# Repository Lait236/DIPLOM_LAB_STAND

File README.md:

В DIPLOM_LAB_STAND_SCHEMES находятся принципиальные схемы стенда и разводки плат в вариантах с модулями (с использованием заливки земли полигоном ..._gnd или без заливки) и без них (тоже с заливкой полигоном и без неё).

DIPLOM.kicad_sch - Принципиальная схема управляющей платы.

пс_плата_2.kicad_sch - Принципиальная платы расширенной периферии.

DIPLOM.kicad_pcb - Разводка управляющей платы.

DIPLOM_BOARD2.kicad_pcb - Разводка платы расширенной периферии.

В DIPLOM_LAB_STAND находятся файлы проекта для Microchip Studio. 

В DEBUG находится .hex файл для прошивки микроконтроллера. 

DIPLOM_LAB_STAND.atsln - сам проект.

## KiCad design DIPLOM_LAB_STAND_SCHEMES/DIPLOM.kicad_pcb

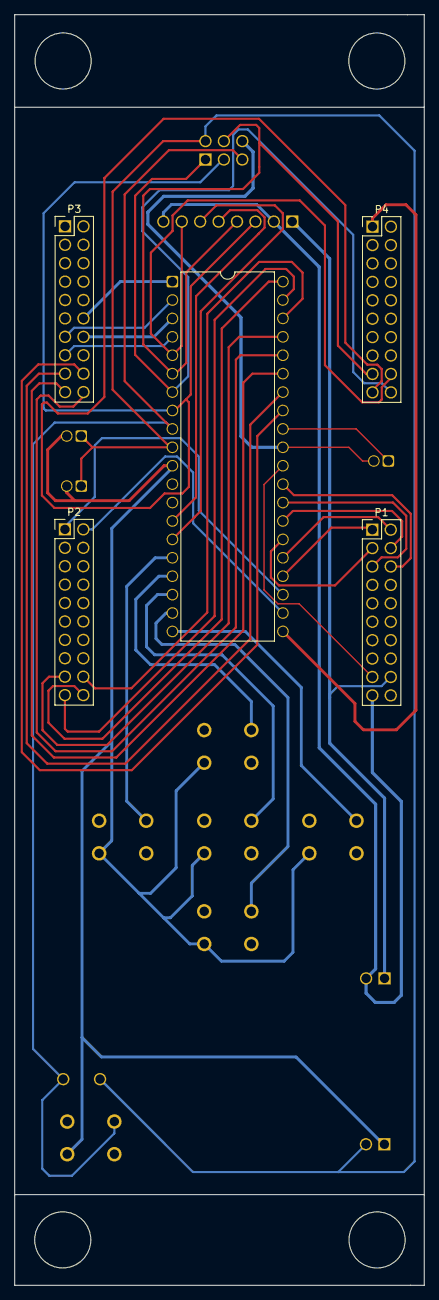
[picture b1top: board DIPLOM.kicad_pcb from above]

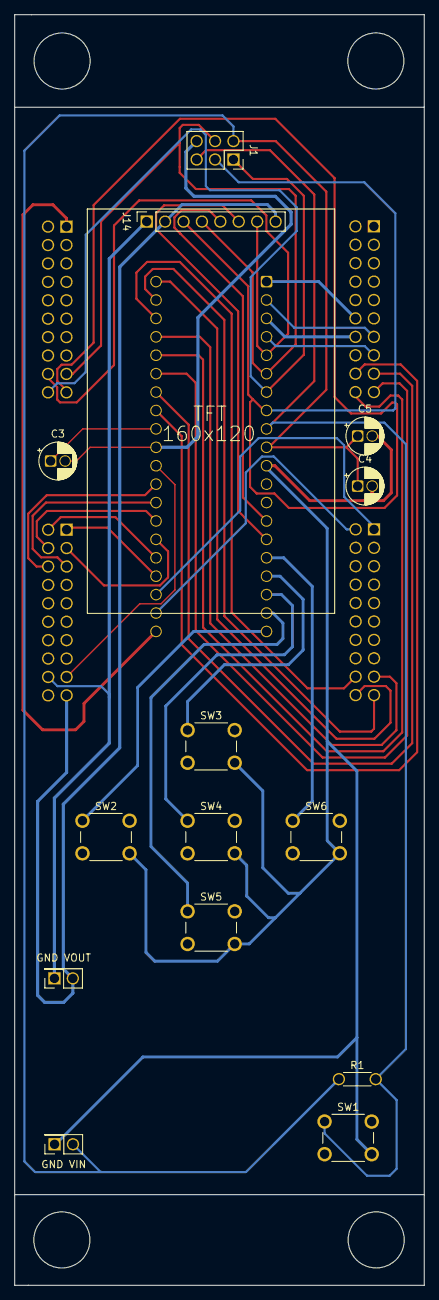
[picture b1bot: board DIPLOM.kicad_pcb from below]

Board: 2 copper layers, 56.5 x 150.0 mm, 19 parts (14 on the bottom side), 37 nets.

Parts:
C3, C5: 0.1uF; CP_Radial_D5.0mm_P2.00mm
C4: 10uF; CP_Radial_D5.0mm_P2.00mm
GND VIN: PinSocket_2x01_P2.54mm_Vertical
GND VOUT: PinSocket_2x01_P2.54mm_Vertical
J1: USBASP_PINS; PinSocket_2x03_P2.54mm_Vertical
J14: display_out; PinSocket_1x08_P2.54mm_Vertical
P1, P2, P3, P4: PinHeader_2x10_P2.54mm_Vertical
R1: 10k; R_Axial_DIN0204_L3.6mm_D1.6mm_P5.08mm_Horizontal
SW1: BTN_RST; SW_PUSH_6mm
SW2: BTN_L; SW_PUSH_6mm
SW3: BTN_UP; SW_PUSH_6mm
SW4: BTN_CENTER; SW_PUSH_6mm
SW5: BTN_DOWN; SW_PUSH_6mm
SW6: BTN_R; SW_PUSH_6mm
U5: ATmega1284P-P; DIP-40_W15.24mm

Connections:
+3.3v: GND VOUT.2, J14.2, J14.8, P1.19
+5.0v: C4.1, C5.1, GND VIN.2, J1.2 (VCC), P1.17, R1.1, U5.10 (VCC), U5.30 (AVCC)
GND: C3.2, C4.2, C5.2, GND VIN.1, GND VOUT.1, J1.6 (GND), J14.1, P1.18, SW1.1 (A), SW1.2 (A), SW2.2 (A), SW3.2 (A), SW4.2 (A), SW5.2 (A), SW6.2 (A), U5.11 (GND), U5.31 (GND)
unnamed: J1.1 (MISO), P4.20, U5.7 (PB6)
unnamed: J1.4 (MOSI), J14.4, P4.17, U5.6 (PB5)
unnamed: J1.3 (SCK), J14.3, P4.19, U5.8 (PB7)
unnamed: J1.5 (~RST), R1.2, SW1.1 (A), U5.9 (~RESET)
unnamed: P2.20, U5.40 (PA0)
unnamed: P2.19, U5.39 (PA1)
unnamed: P2.18, U5.38 (PA2)
unnamed: P2.17, U5.37 (PA3)
unnamed: P3.20, U5.36 (PA4)
unnamed: P3.19, U5.35 (PA5)
unnamed: P3.17, U5.34 (PA6)
unnamed: P3.18, U5.33 (PA7)
unnamed: P3.12, U5.1 (PB0)
unnamed: P3.13, U5.2 (PB1)
unnamed: P3.14, U5.3 (PB2)
unnamed: P3.15, U5.4 (PB3)
unnamed: P2.2, U5.22 (PC0)
unnamed: P2.1, U5.23 (PC1)
unnamed: P1.1, U5.24 (PC2)
unnamed: P1.2, U5.25 (PC3)
unnamed: P1.3, U5.26 (PC4)
unnamed: P1.4, U5.27 (PC5)
unnamed: P1.5, U5.28 (PC6)
unnamed: P1.6, U5.29 (PC7)
unnamed: P4.1, U5.21 (PD7)
unnamed: J14.7, P4.18, U5.5 (PB4)
unnamed: J14.5, U5.14 (PD0)
unnamed: J14.6, U5.15 (PD1)
unnamed: C3.1, U5.32 (AREF)
unnamed: SW6.1 (A), SW6.2 (A), U5.16 (PD2)
unnamed: SW3.1 (A), SW3.2 (A), U5.17 (PD3)
unnamed: SW4.1 (A), SW4.2 (A), U5.18 (PD4)
unnamed: SW5.1 (A), SW5.2 (A), U5.19 (PD5)
unnamed: SW2.1 (A), SW2.2 (A), U5.20 (PD6)

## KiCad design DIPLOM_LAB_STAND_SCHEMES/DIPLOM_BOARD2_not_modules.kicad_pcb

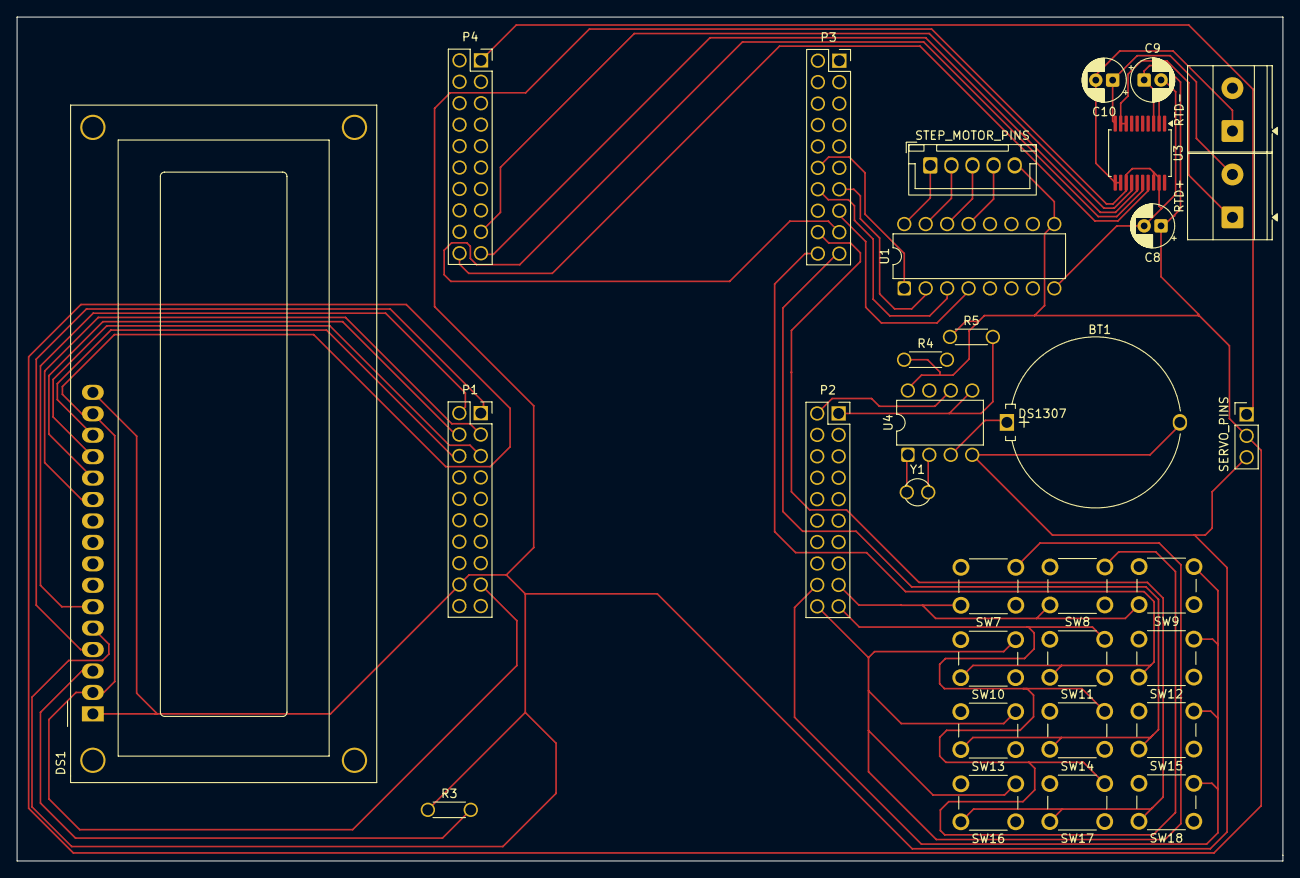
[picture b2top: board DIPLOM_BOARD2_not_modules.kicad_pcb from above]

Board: 2 copper layers, 150.0 x 100.0 mm, 32 parts (0 on the bottom side), 33 nets.

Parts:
BT1: Battery 3V; Battery_Panasonic_CR2032-HFN_Horizontal_CircularHoles
C8, C9: 0.1uF; CP_Radial_D5.0mm_P2.00mm
C10: 100nF; CP_Radial_D5.0mm_P2.00mm
DS1: WC1602A
P1, P2, P3, P4: PinSocket_2x10_P2.54mm_Vertical
R3: 2k; R_Axial_DIN0204_L3.6mm_D1.6mm_P5.08mm_Horizontal
R4, R5: 4.7k; R_Axial_DIN0204_L3.6mm_D1.6mm_P5.08mm_Horizontal
RTD+: TerminalBlock_Phoenix_MKDS-1,5-2-5.08_1x02_P5.08m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; TerminalBlock_Phoenix_MKDS-1,5-2-5.08_1x02_P5.08mm_Horizont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
RTD-: TerminalBlock_Phoenix_MKDS-1,5-2-5.08_1x02_P5.08m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; TerminalBlock_Phoenix_MKDS-1,5-2-5.08_1x02_P5.08mm_Horizont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
SERVO_PINS: PinHeader_1x03_P2.54mm_Vertical
STEP_MOTOR_PINS: JST_XH_B5B-XH-A_1x05_P2.50mm_Vertical
SW7: 1; SW_PUSH_6mm
SW8: 2; SW_PUSH_6mm
SW9: 3; SW_PUSH_6mm
SW10: 4; SW_PUSH_6mm
SW11: 5; SW_PUSH_6mm
SW12: 6; SW_PUSH_6mm
SW13: 7; SW_PUSH_6mm
SW14: 8; SW_PUSH_6mm
SW15: 9; SW_PUSH_6mm
SW16: *; SW_PUSH_6mm
SW17: 0; SW_PUSH_6mm
SW18: #; SW_PUSH_6mm
U1: ULN2003; DIP-16_W7.62mm
U3: MAX31865xAP; SSOP-20_5.3x7.2mm_P0.65mm
U4: DS1307; DIP-8_W7.62mm
Y1: 32.768kHz; Crystal_AT310_D3.0mm_L10.0mm_Vertical

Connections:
+5.0v: C8.1, C9.1, DS1.2 (VDD), DS1.15 (LED(+)), P1.17, R4.1, R5.1, SERVO_PINS.2, STEP_MOTOR_PINS.5, U1.9 (COM), U3.2 (DVDD), U3.3 (VDD), U4.8 (VCC)
GND: BT1.2 (-), C8.2, C9.2, DS1.1 (VSS), DS1.5 (R/W), DS1.16 (LED(-)), P1.18, R3.1, SERVO_PINS.3, U1.8 (GND), U3.13 (GND), U3.18 (DGND), U3.19 (GND), U4.4 (GND)
unnamed: BT1.1 (+), U4.3 (VBAT)
unnamed: DS1.3 (VO), R3.2
unnamed: P4.20, U3.17 (SDO)
unnamed: P4.17, U3.14 (SDI)
unnamed: P4.19, U3.15 (SCLK)
unnamed: P2.20, SW7.2 (A), SW10.2 (A), SW13.2 (A), SW16.2 (A)
unnamed: P2.19, SW8.2, SW11.2, SW14.2, SW17.2
unnamed: P2.18, SW9.2, SW12.2, SW15.2, SW18.2
unnamed: P2.17, SW7.1 (A), SW8.1, SW9.1
unnamed: P3.20, SW10.1 (A), SW11.1, SW12.1
unnamed: P3.19, SW13.1 (A), SW14.1, SW15.1
unnamed: P3.18, SW16.1 (A), SW17.1, SW18.1
unnamed: P3.17, U3.16 (~CS)
unnamed: P3.12, U1.1 (I1)
unnamed: P3.13, U1.2 (I2)
unnamed: P3.14, U1.3 (I3)
unnamed: P3.15, U1.4 (I4)
unnamed: P2.2, R4.2, U4.6 (SCL)
unnamed: P2.1, R5.2, U4.5 (SDA)
unnamed: DS1.4 (RS), P1.1
unnamed: DS1.6 (E), P1.2
unnamed: DS1.11 (D4), P1.3
unnamed: DS1.12 (D5), P1.4
unnamed: DS1.13 (D6), P1.5
unnamed: DS1.14 (D7), P1.6
unnamed: P4.1, SERVO_PINS.1
unnamed: U3.4 (BIAS), U3.5 (REFIN+), U3.6 (REFIN-), U3.7 (ISENSOR)
unnamed: C10.1, RTD+.1, RTD+.2, U3.8 (FORCE+), U3.9 (FORCE2), U3.10 (RTDIN+)
unnamed: C10.2, RTD-.1, U3.11 (RTDIN-), U3.12 (FORCE-)
unnamed: U4.1 (X1), Y1.1
unnamed: U4.2 (X2), Y1.2

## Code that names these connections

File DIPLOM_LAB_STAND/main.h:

	/*
 * main.h
 *
 * Created: 02.04.2026 22:29:26
 *  Author: Владислав
 */ 


#ifndef MAIN_H_
#define MAIN_H_

// установка частоты

#define F_CPU 8000000UL

// подключение системных файлов библиотек

#include <avr/io.h> // стандартная библиотека инициализации AVR
#include <util/delay.h> // задержки
#include <stdint.h> // фиксированные целочисленные типы
#include <avr/pgmspace.h> // работа с памятью программ Flash || PROGMEM хранит большие таблицы не в SRAM, а во Flash, так как SRAM мало || обращение к Flash памяти идет через оператор &
#include <avr/interrupt.h> // работа с прерываниями

// замена имен лапок на макроподстановки для удобной инициализации spi для дисплея

#define LCD_SCK  PB7 // пин тактового сигнала SPI
#define LCD_MOSI PB5 // пин MOSI SPI
#define LCD_CS   PB4 // пин Chip Select дисплея подключён к PB2 || 0 — дисплей выбран и слушает SPI || 1 — дисплей игнорирует SPI
#define LCD_DC   PD1 // пин DC дисплея подключён к PD1 || DC = Data / Command || 0 — отправляем команду || 1 — отправляем данные
#define LCD_RST  PD0 // пин аппаратного сброса дисплея подключён к PD0

// назначение для отрисовки на дисплее

#define LCD_XSTART 0 // смещение по X (LCD_XSTART поправка по горизонтали)
#define LCD_YSTART 0 // смещение по Y (LCD_YSTART поправка по вертикали)
#define LCD_MADCTL 0xC0 // значение для команды MADCTL || оно управляет ориентацией экрана и порядком обхода памяти(описание приведено в документации на ST7735)

// макроподстановки для цветов в формате RGB565 (начальная палитра || сайт для подбора значения цветов в формате RGB565:https://rgbcolorpicker.com/565)

#define COLOR_BLACK  0x0000 // чёрный цвет
#define COLOR_WHITE  0xFFFF // белый цвет
#define COLOR_RED    0xF800 // красный цвет
#define COLOR_GREEN  0x07E0 // зелёный цвет
#define COLOR_BLUE   0x001F // синий цвет
#define COLOR_YELLOW 0xFFE0 // жёлтый цвет

// крестовина для управления системой

#define BTN_LEFT   PD2 // левая кнопка
#define BTN_UP     PD3 // верхняя кнопка
#define BTN_CENTER PD4 // центральная кнопка
#define BTN_DOWN   PD5 // нижняя кнопка
#define BTN_RIGHT  PD6 // правая кнопка


// макроподстановка для клавиатуры

#define KEY_NONE 0 // значение, которое возвращает клавиатура, если кнопка не нажата

// макроподстановки для режимов экранов

#define SCREEN_HOME           0 // главный экран
#define SCREEN_BOARD_SELECT   1 // экран выбора платы
#define SCREEN_BOARD2_MENU    2 // меню платы №2
#define SCREEN_KEYBOARD_TEST  3 // тест клавиатуры
#define SCREEN_SERVO_TEST     4 // тест сервопривода
#define SCREEN_STEPPER_TEST   5 // тест шагового мотора
#define SCREEN_BOARD1_MENU    6 // меню платы №1
#define SCREEN_SEVEN_SEGMENT_TEST 7 // экран теста семисегментных индикаторов
#define SCREEN_LED_BAR_TEST 8 // экран теста 8 светодиодов
#define SCREEN_SPEAKER_TEST 9 // экран теста спикера
#define SCREEN_RTC_TEST 10 // экран теста часов реального времени
#define SCREEN_TEMP_LCD_TEST 11 // экран теста MAX31865 и LCD 16x2

// макроподстановки для меню платы №1

#define BOARD1_MENU_COUNT 3 // общее количество пунктов меню платы №1
#define BOARD1_MENU_VISIBLE 3 // количество пунктов меню, которые одновременно видны на экране

// макроподстановки для пунктов меню платы №1

#define BOARD1_MENU_ITEM_SEVEN_SEGMENT_TEST 0 // первый пункт меню платы №1: тест семисегментных индикаторов
#define BOARD1_MENU_ITEM_LED_BAR_TEST 1 // второй пункт меню платы №1: тест 8 светодиодов
#define BOARD1_MENU_ITEM_SPEAKER_TEST 2 // третий пункт меню платы №1: тест спикера

// макроподстановки для меню платы №2

#define MENU_COUNT 5 // общее количество пунктов меню платы №2
#define MENU_VISIBLE 4 // количество пунктов меню, которые одновременно видны на экране

// макроподстановки для пунктов меню платы №2

#define MENU_ITEM_KEYBOARD_TEST 0 // первый пункт меню платы №2: тест клавиатуры
#define MENU_ITEM_SERVO_TEST    1 // второй пункт меню платы №2: тест сервопривода
#define MENU_ITEM_STEPPER_TEST 2 // третий пункт меню платы №2: тест шагового мотора
#define MENU_ITEM_TEMP_LCD_TEST 3 // четвертый пункт меню платы №2: тест MAX31865 и LCD 16x2
#define MENU_ITEM_RTC_TEST 4 // пятый пункт меню платы №2: тест DS1307 (часов реального времени)

// объявления глобальных переменные для управления меню

extern uint8_t menu_selected;
extern uint8_t menu_top;
extern uint8_t screen_mode;

#endif /* MAIN_H_ */

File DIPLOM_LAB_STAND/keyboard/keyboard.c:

/*
 * keyboard.c
 *
 * Created: 02.04.2026 1:49:12
 *  Author: Владислав
 */ 


#include "../main.h"
#include "keyboard.h"

// все функции, объявленные через static,
// являются служебными и не подразумевают вызов извне

#define KEYPAD_COL1 PA0 // первый столбец клавиатуры
#define KEYPAD_COL2 PA1 // второй столбец клавиатуры
#define KEYPAD_COL3 PA2 // третий столбец клавиатуры
#define KEYPAD_ROW1 PA3 // первая строка клавиатуры
#define KEYPAD_ROW2 PA4 // вторая строка клавиатуры
#define KEYPAD_ROW3 PA5 // третья строка клавиатуры
#define KEYPAD_ROW4 PA6 // четвёртая строка клавиатуры

// настройка портов клавиатуры

void keypad_init(void)
{
	DDRA |= (1 << KEYPAD_COL1) | (1 << KEYPAD_COL2) | (1 << KEYPAD_COL3); // вывод PA0, PA1, PA2 устанавливаем на вход	- это столбцы клавиатуры

	PORTA |= (1 << KEYPAD_COL1) | (1 << KEYPAD_COL2) | (1 << KEYPAD_COL3); // устанавливаем все столбцы в 1 - это неактивное состояние

	DDRA &= ~((1 << KEYPAD_ROW1) | (1 << KEYPAD_ROW2) | (1 << KEYPAD_ROW3) | (1 << KEYPAD_ROW4)); // вывод PA4, PA5, PA6, PA7 устанавливаем на вход - это строки клавиатуры

	PORTA |= (1 << KEYPAD_ROW1) | (1 << KEYPAD_ROW2) | (1 << KEYPAD_ROW3) | (1 << KEYPAD_ROW4); // устанавливаем подтяжку на строки	|| пока кнопка не нажата, вход читает 1
}

// устанавливаем все столбцы клавиатуры в 1

static void keypad_all_columns_high(void)
{
	PORTA |= (1 << KEYPAD_COL1) | (1 << KEYPAD_COL2) | (1 << KEYPAD_COL3); // вывод PA0 = 1, PA1 = 1, PA2 = 1
}

// выбираем один столбец клавиатуры

static void keypad_select_column(uint8_t column)
{
	keypad_all_columns_high(); // сначала все столбцы устанавливаем в 1
	
	// если выбран столбец 0, опускаем PA0 в 0
	if (column == 0)
	{
		PORTA &= ~(1 << KEYPAD_COL1);
	}
	
	// если выбран столбец 1, опускаем PA1 в 0
	if (column == 1)
	{
		PORTA &= ~(1 << KEYPAD_COL2);
	}

	// если выбран столбец 2, опускаем PA2 в 0
	if (column == 2)
	{
		PORTA &= ~(1 << KEYPAD_COL3);
	}
	
}

// прочитать строки клавиатуры
// вследствие подтяжки:
// 1 — кнопка не нажата
// 0 — кнопка нажата

static uint8_t keypad_read_row(void)
{
	if (!(PINA & (1 << KEYPAD_ROW1)))
	{
		return 0; // если PA4 стал 0, нажата строка 0
	}
	if (!(PINA & (1 << KEYPAD_ROW2)))
	{
		return 1; // если PA5 стал 0, нажата строка 1
	}
	
	if (!(PINA & (1 << KEYPAD_ROW3)))
	{
		return 2; // если PA6 стал 0, нажата строка 2
	}
	
	if (!(PINA & (1 << KEYPAD_ROW4)))
	{
		return 3; // если PA7 стал 0, нажата строка 3
	}

	return 255; // если ни одна строка не нажата
}

// получаем одну нажатую клавишу, если ничего не нажато, возвращаем KEY_NONE

char keypad_get_key(void)
{
	uint8_t column; // номер проверяемого столбца

	uint8_t row; // номер найденной строки

	for (column = 0; column < 3; column++)
	{
		// по очереди проверяем 3 столбца

		keypad_select_column(column); // делаем выбранный столбец равным 0
		_delay_us(5); // задержка

		row = keypad_read_row(); // проверяем, какая строка стала 0

		if (row != 255)
		{
			// если найдена нажатая строка

			_delay_ms(20); // антидребезг - ждём 20 мс

			if (keypad_read_row() == row)
			{
				// проверяем, что кнопка всё ещё нажата

				while (keypad_read_row() != 255);
				
				_delay_ms(20); // антидребезг при отпускании

				keypad_all_columns_high(); // возвращаем все столбцы в 1

				return keymap[row][column]; // возвращаем символ из таблицы keymap
			}
		}
	}

	keypad_all_columns_high(); // если ничего не нашли, всё равно возвращаем столбцы в 1

	return KEY_NONE; // кнопка не нажата
}

// быстрое чтение клавиатуры без ожидания отпускания, нужно для режимов, где кнопка должна работать при удержании

static char keypad_scan_raw(void)
{
	uint8_t column;
	uint8_t row;

	for (column = 0; column < 3; column++)
	{
		keypad_select_column(column); // выбираем очередной столбец клавиатуры

		_delay_us(5);

		row = keypad_read_row(); // читаем строки клавиатуры

		if (row != 255)
		{
			// если какая-либо строка стала 0, значит кнопка нажата

			keypad_all_columns_high(); // возвращаем все столбцы в 1

			return keymap[row][column]; // возвращаем символ нажатой кнопки
		}
	}

	keypad_all_columns_high(); // если ничего не нажато, тоже возвращаем все столбцы в 1

	return KEY_NONE; // кнопка не нажата
}

// специальное чтение клавиатуры
// кнопки 4 и 6 разрешено удерживать
// остальные кнопки возвращаются один раз за нажатие

char keypad_get_key_stepper(void)
{
	static char last_key = KEY_NONE; // последняя прочитанная клавиша

	char key; // текущая прочитанная клавиша

	key = keypad_scan_raw(); // читаем клавиатуру без ожидания отпускания кнопки

	if (key == KEY_NONE)
	{
		// если кнопка не нажата

		last_key = KEY_NONE; // сбрасываем память о последней клавише

		return KEY_NONE; // ничего не возвращаем
	}

	_delay_ms(5); //  задержка

	if (key != keypad_scan_raw())
	{
		// если через 5 мс клавиша уже другая или исчезла, значит это мог быть дребезг

		return KEY_NONE; // игнорируем такое нажатие
	}

	if (key == '4' || key == '6')
	{
		// кнопки 4 и 6 разрешаем возвращать постоянно, пока кнопка удерживается

		last_key = key; // запоминаем последнюю клавишу

		return key; // возвращаем 4 или 6 каждый раз, пока кнопка зажата
	}

	if (key != last_key)
	{
		// если это новая клавиша, которую раньше не держали

		last_key = key; // запоминаем данную клавишу

		return key; // возвращаем один раз
	}

	return KEY_NONE; // если это не 4 и не 6, и кнопка всё ещё удерживается, повторно её не возвращаем
}

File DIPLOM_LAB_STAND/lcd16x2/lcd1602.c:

/*
 * lcd1602.c
 *
 * Created: 20.05.2026 1:52:18
 *  Author: Владислав
 */ 


#include "../main.h"
#include "lcd1602.h"

// назначение выводов LCD 16x2

#define LCD1602_PORT PORTC
#define LCD1602_DDR  DDRC

#define LCD1602_RS PC2
#define LCD1602_E  PC3

#define LCD1602_D4 PC4
#define LCD1602_D5 PC5
#define LCD1602_D6 PC6
#define LCD1602_D7 PC7

#define LCD1602_MASK ((1 << LCD1602_RS) | (1 << LCD1602_E) | (1 << LCD1602_D4) | (1 << LCD1602_D5) | (1 << LCD1602_D6) | (1 << LCD1602_D7))

// отключение JTAG

static void lcd1602_disable_jtag(void)
{
	uint8_t sreg;
	uint8_t mcucr_value;

	sreg = SREG; // сохраняем состояние флага глобальных прерываний

	cli();

	mcucr_value = MCUCR | (1 << JTD); // берём текущее значение MCUCR и добавляем бит JTD

	// дважды записываем JTD = 1
	MCUCR = mcucr_value;
	MCUCR = mcucr_value;

	SREG = sreg; // возвращаем состояние прерываний
}

// управление линией E

static void lcd1602_e_pulse(void)
{
	LCD1602_PORT |= (1 << LCD1602_E);
	_delay_us(50);

	LCD1602_PORT &= ~(1 << LCD1602_E);
	_delay_us(50);
}

// отправка половины байта, очищаем только линии D4..D7

static void lcd1602_send_halfbyte(uint8_t halfbyte)
{
	LCD1602_PORT &= ~((1 << LCD1602_D4) | (1 << LCD1602_D5) | (1 << LCD1602_D6) | (1 << LCD1602_D7));

	if (halfbyte & 0b00000001)
	{
		LCD1602_PORT |= (1 << LCD1602_D4);
	}

	if (halfbyte & 0b00000010)
	{
		LCD1602_PORT |= (1 << LCD1602_D5);
	}

	if (halfbyte & 0b00000100)
	{
		LCD1602_PORT |= (1 << LCD1602_D6);
	}

	if (halfbyte & 0b00001000)
	{
		LCD1602_PORT |= (1 << LCD1602_D7);
	}

	lcd1602_e_pulse();
}

// отправка байта

static void lcd1602_send_byte(uint8_t data, uint8_t mode)
{
	if (mode == 0)
	{
		LCD1602_PORT &= ~(1 << LCD1602_RS); // вывод RS = 0 — команда
	}
	else
	{
		LCD1602_PORT |= (1 << LCD1602_RS); // вывод RS = 1 — данные
	}

	lcd1602_send_halfbyte(data >> 4); // сначала старшая половина байта

	lcd1602_send_halfbyte(data & 0x0F); // потом младшая половина байта
}

// передаем команду

static void lcd1602_command(uint8_t command)
{
	lcd1602_send_byte(command, 0);
}

// передаем символ

static void lcd1602_char(uint8_t data)
{
	lcd1602_send_byte(data, 1);
}

// инициализация LCD 16x2

void lcd1602_init(void)
{
	lcd1602_disable_jtag(); // освобождаем PC2..PC5 от JTAG

	LCD1602_DDR |= LCD1602_MASK; // выводы RS, E, D4..D7 делаем выходами

	LCD1602_PORT &= ~LCD1602_MASK; // устанавливаем сначала всё в 0

	_delay_ms(15);

	lcd1602_send_halfbyte(0b00000011);
	_delay_ms(4);

	lcd1602_send_halfbyte(0b00000011);
	_delay_us(100);

	lcd1602_send_halfbyte(0b00000011);
	_delay_ms(1);

	lcd1602_send_halfbyte(0b00000010);
	_delay_ms(1);
	
	// переводим LCD в 4-битный режим

	lcd1602_command(0b00101000); // 4-битный режим, 2 строки, шрифт 5x8

	lcd1602_command(0b00001100); // дисплей включён, курсор выключен

	lcd1602_command(0b00000110); // автоинкремент адреса

	lcd1602_clear(); // очищаем экран
}

// очищаем LCD

void lcd1602_clear(void)
{
	lcd1602_command(0b00000001);
	_delay_ms(2);
}

// устанавливаем позицию

void lcd1602_set_pos(uint8_t x, uint8_t y)
{
	uint8_t address;

	if (y == 0)
	{
		address = 0x00 + x;
	}
	else
	{
		address = 0x40 + x;
	}

	lcd1602_command(0b10000000 | address);
}

// выводим строку

void lcd1602_print_string(char str[])
{
	uint8_t i;

	for (i = 0; str[i] != '\0'; i++)
	{
		lcd1602_char(str[i]);
	}
}

// выключаем LCD

void lcd1602_off(void)
{
	lcd1602_command(0b00001000); // значение DISPLAY OFF

	LCD1602_PORT &= ~LCD1602_MASK; // все линии LCD в 0

	LCD1602_DDR &= ~LCD1602_MASK; // освобождаем PC2..PC7
}

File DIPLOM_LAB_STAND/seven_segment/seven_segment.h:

/*
 * seven_segment.h
 *
 * Created: 10.05.2026 21:07:24
 *  Author: Владислав
 */ 


#ifndef SEVEN_SEGMENT_H_
#define SEVEN_SEGMENT_H_

#include <stdint.h>

void seven_segment_init(void); // инициализируем семисегментные индикаторы
// сегменты: PORTA
// разряды: PB0, PB1, PB2, PB3

void seven_segment_enable(void); // разрешаем отображение числа
void seven_segment_disable(void); // выключаем все разряды и гасим сегменты
void seven_segment_set_number(uint16_t num); // выводим число 0..9999

void seven_segment_set_digits(uint8_t thousands, uint8_t hundreds, uint8_t tens, uint8_t units); // задаём 4 цифры вручную:
// значение THOUSANDS — тысячи,
// значение HUNDREDS — сотни,
// значение TENS — десятки,
// значение UNITS — единицы


#endif /* SEVEN_SEGMENT_H_ */
